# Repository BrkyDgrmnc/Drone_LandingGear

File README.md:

# Drone_LandingPod <br/>

## Proje Bilgileri<br/>

  Bu proje, döner kanatlı insansız hava araçlarında kullanılmak üzere geliştirilmiş iniş takımının elektronik kartını içermektedir. Kart, iki adet 6V DC motoru kontrol etmek üzere tasarlanmıştır. Motorları sürmek için L9110 motor sürücü entegresi kullanılmıştır.<br/>

  <br/>

### Kart Özellikleri <br/>

- Kontrolcü **:** Arduino Pro Mini (ATmega328)<br/>
- Giriş Voltajı **:** 12V *(Not:Kontrolcü için harici 5V girişi gereklidir.)* <br/>
- Motor Çıkış Voltajı **:** 6V<br/>
- Çıkış Akımı **:** 800mA<br/>
- Anlık Tepe Akımı **:** 1500mA<br/>
<br/>

## PCB Görselleri <br/>

  <br/>

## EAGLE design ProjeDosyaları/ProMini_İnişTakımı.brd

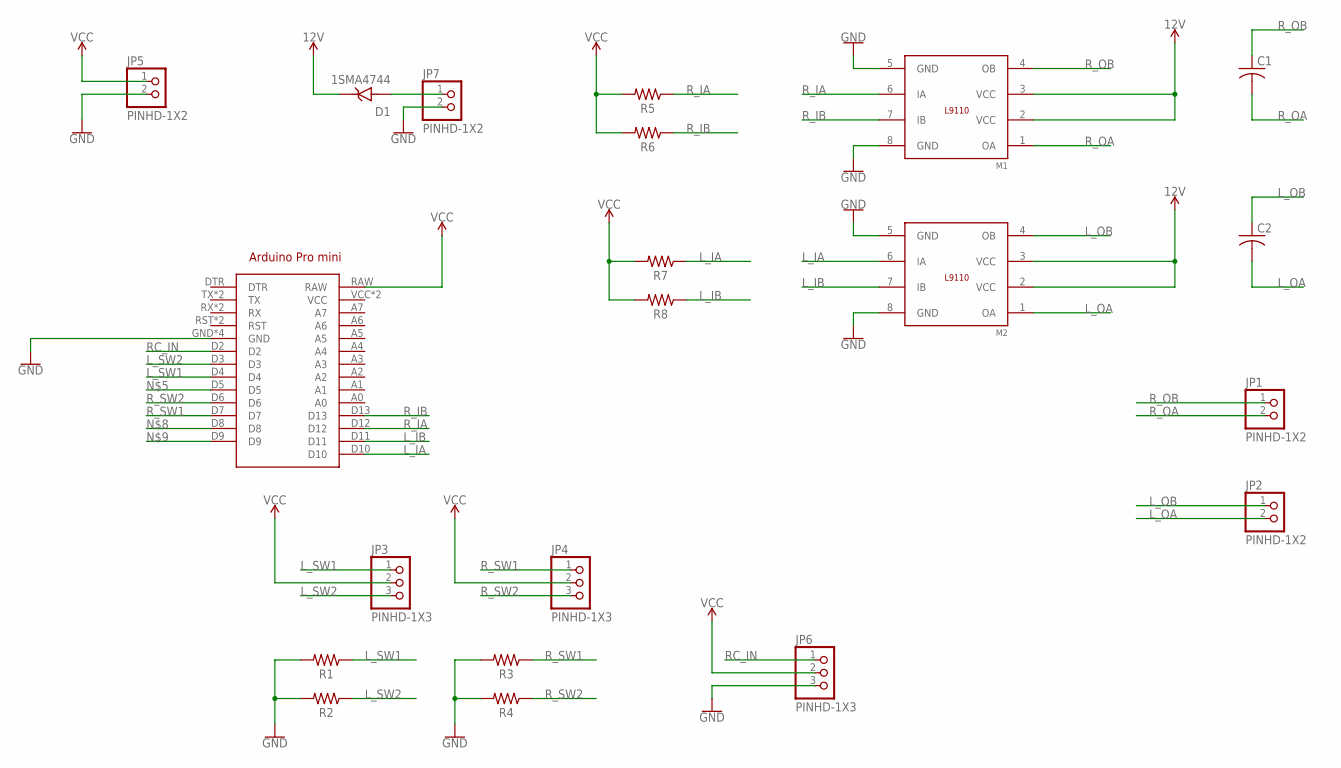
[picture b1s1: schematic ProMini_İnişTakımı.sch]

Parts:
ARDUINO1: ARDUINO_PRO_MINI
C1, C2: C-US_CHIP-0805(2012-METRIC); CAPC2012X110
D1: 1SMA4744; DIOM4325X250N
JP1, JP2, JP5, JP7: PINHD-1X2; 1X02
JP3, JP4, JP6: PINHD-1X3; 1X03
M1, M2: L9110; SO8P
R1, R2, R3, R4, R5, R6, R7, R8: R-US_CHIP-0805(2012-METRIC); RESC2012X65

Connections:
12V: D1.C (K), M1.2 (VCC), M1.3 (VCC), M2.2 (VCC), M2.3 (VCC)
GND: ARDUINO1.GND, ARDUINO1.GND@1 (GND), ARDUINO1.GND@2 (GND), ARDUINO1.GND@3 (GND), JP5.2, JP6.3, JP7.2, M1.5 (GND), M1.8 (GND), M2.5 (GND), M2.8 (GND), R1.2, R2.2, R3.2, R4.2
L_IA: ARDUINO1.D10, M2.6 (IA), R7.1
L_IB: ARDUINO1.D11, M2.7 (IB), R8.1
L_OA: C2.2, JP2.2, M2.1 (OA)
L_OB: C2.1, JP2.1, M2.4 (OB)
L_SW1: ARDUINO1.D4, JP3.1, R1.1
L_SW2: ARDUINO1.D3, JP3.3, R2.1
unnamed: D1.A, JP7.1
RC_IN: ARDUINO1.D2, JP6.1
R_IA: ARDUINO1.D12, M1.6 (IA), R5.1
R_IB: ARDUINO1.D13, M1.7 (IB), R6.1
R_OA: C1.2, JP1.2, M1.1 (OA)
R_OB: C1.1, JP1.1, M1.4 (OB)
R_SW1: ARDUINO1.D7, JP4.1, R3.1
R_SW2: ARDUINO1.D6, JP4.3, R4.1
VCC: ARDUINO1.RAW, ARDUINO1.VCC, ARDUINO1.VCC@1 (VCC), JP3.2, JP4.2, JP5.1, JP6.2, R5.2, R6.2, R7.2, R8.2

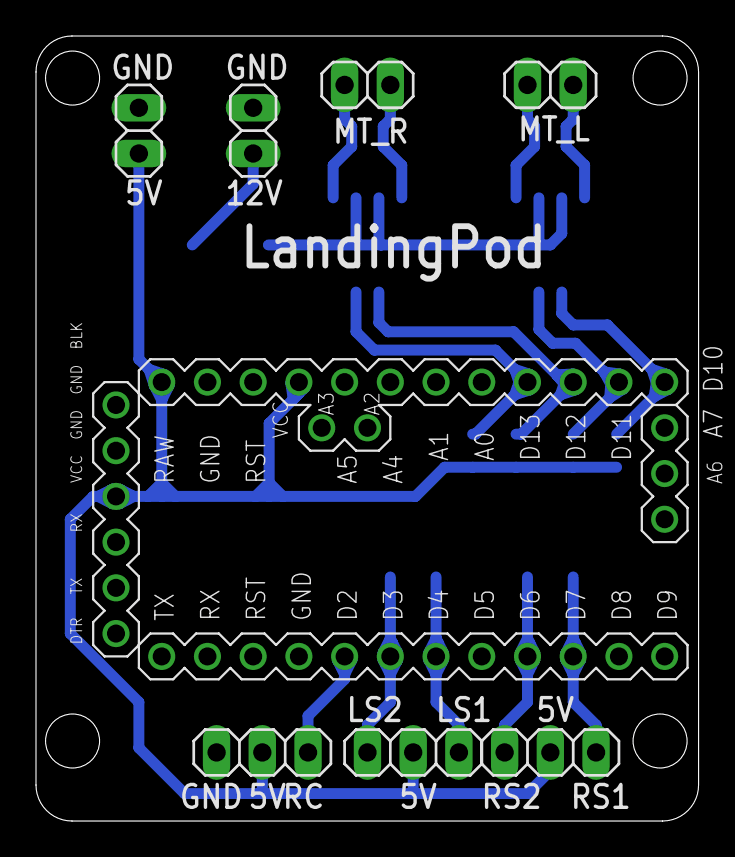
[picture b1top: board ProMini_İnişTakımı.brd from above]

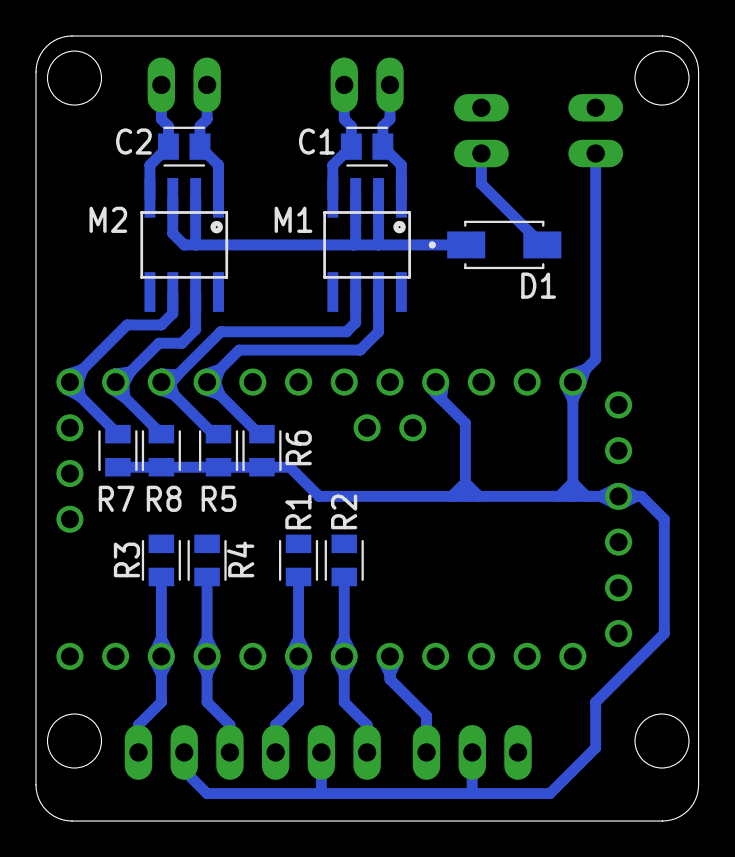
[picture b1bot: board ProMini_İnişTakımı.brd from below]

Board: 2 copper layers, 36.8 x 43.6 mm, 21 parts (13 on the bottom side), 17 nets.

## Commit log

2024-02-16 Create Resimler
2024-02-16 Rename ProMini_niTakm

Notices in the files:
parts and their libraries:
SparkFun-Aesthetics: Licensing: Creative Commons ShareAlike 4.0 International - https://creativecommons.org/licenses/by-sa/4.0
